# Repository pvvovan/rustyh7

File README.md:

# rustyh7
stm32h723zg simple app in Rust

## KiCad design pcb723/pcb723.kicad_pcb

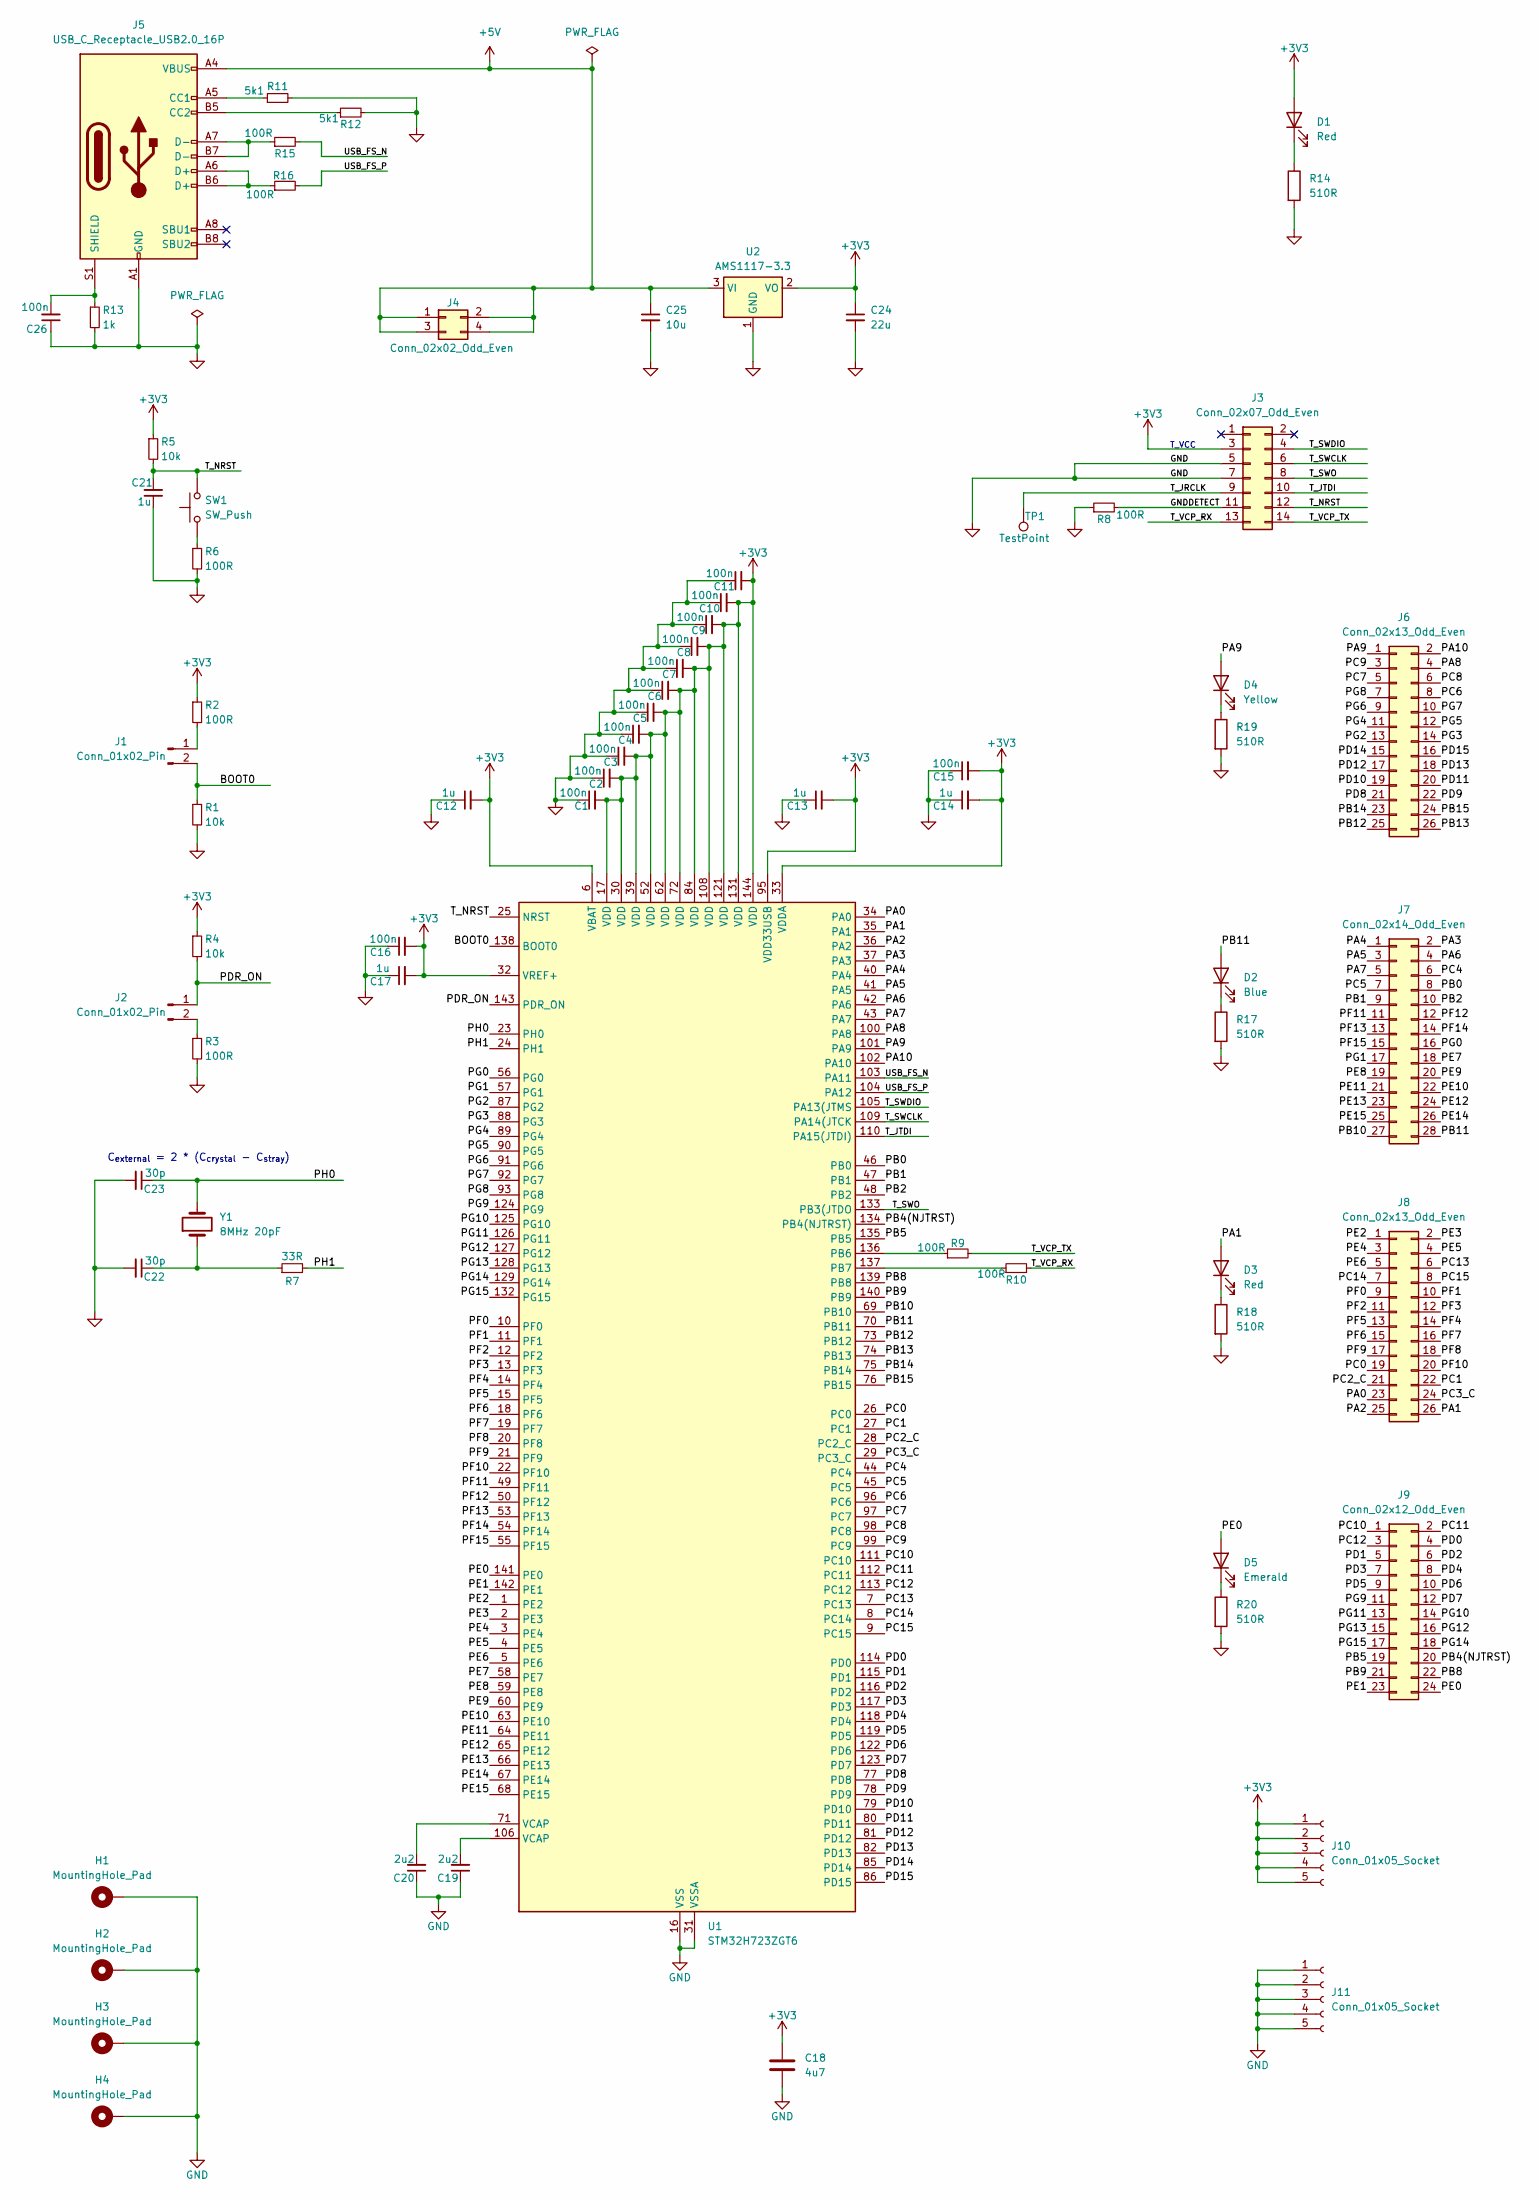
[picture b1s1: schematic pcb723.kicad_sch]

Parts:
C1, C2, C3, C4, C5, C6, C7, C8, C9, C10, C11, C15, C16, C26: 100n; C_0402_1005Metric; JLC# C307331
C12, C13, C14, C17, C21: 1u; C_0402_1005Metric; JLC# C52923
C18: 4u7; C_1206_3216Metric; JLC# C29823
C19, C20: 2u2; C_0805_2012Metric; JLC# C377773
C22, C23: 30p; C_0603_1608Metric; JLC# C1658
C24: 22u; C_0805_2012Metric; JLC# C45783
C25: 10u; C_1206_3216Metric; JLC# C13585
D1: Red; LED_0603_1608Metric; JLC# C2286
D2: Blue; LED_0805_2012Metric
D3: Red; LED_0805_2012Metric; JLC# C84256
D4: Yellow; LED_0805_2012Metric; JLC# C2296
D5: Emerald; LED_0805_2012Metric; JLC# C2297
H1, H2, H3, H4: MountingHole_Pad; MountingHole_3.2mm_M3_Pad_Via
J1, J2: Conn_01x02_Pin; PinHeader_1x02_P2.54mm_Vertical
J3: Conn_02x07_Odd_Even; PinHeader_2x07_P1.27mm_Vertical_SMD
J4: Conn_02x02_Odd_Even; PinSocket_2x02_P2.54mm_Vertical
J5: USB_C_Receptacle_USB2.0_16P; USB_C_Receptacle_GCT_USB4105-xx-A_16P_TopMnt_Horizontal
J6, J8: Conn_02x13_Odd_Even; PinSocket_2x13_P2.54mm_Vertical
J7: Conn_02x14_Odd_Even; PinSocket_2x14_P2.54mm_Vertical
J9: Conn_02x12_Odd_Even; PinSocket_2x12_P2.54mm_Vertical
J10, J11: Conn_01x05_Socket; PinSocket_1x05_P2.54mm_Vertical
R1, R4, R5: 10k; R_0402_1005Metric; JLC# C25744
R2, R3, R6, R8, R9, R10, R15, R16: 100R; R_0402_1005Metric; JLC# C25076
R7: 33R; R_0402_1005Metric; JLC# C25105
R11, R12: 5k1; R_0402_1005Metric; JLC# C25905
R13: 1k; R_0402_1005Metric; JLC# C11702
R14, R17, R18, R19, R20: 510R; R_0805_2012Metric_Pad1.20x1.40mm_HandSolder; JLC# C17734
SW1: SW_Push; SW_Push_1P1T_NO_6x6mm_H9.5mm
TP1: TestPoint; TestPoint_Plated_Hole_D2.0mm
U1: STM32H723ZGT6; LQFP-144_20x20mm_P0.5mm
U2: AMS1117-3.3; SOT-223-3_TabPin2; JLC# C6186
Y1: 8MHz 20pF; Crystal_SMD_5032-2Pin_5.0x3.2mm; JLC# C115962

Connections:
+3V3: C1.2, C2.2, C3.2, C4.2, C5.2, C6.2, C7.2, C8.2, C9.2, C10.2, C11.2, C12.2, C13.2, C14.2, C15.2, C16.2, C17.2, C18.1, C24.1, D1.2 (A), J3.3, J10.1, J10.2, J10.3, J10.4, J10.5, R2.1, R4.1, R5.1, U1.6 (VBAT), U1.17 (VDD), U1.30 (VDD), U1.32 (VREF+), U1.33 (VDDA), U1.39 (VDD), U1.52 (VDD), U1.62 (VDD), U1.72 (VDD), U1.84 (VDD), U1.95 (VDD33USB), U1.108 (VDD), U1.121 (VDD), U1.131 (VDD), U1.144 (VDD), U2.2 (VO)
+5V: C25.1, J4.1, J4.2, J4.3, J4.4, J5.A4 (VBUS), J5.A9 (VBUS), J5.B4 (VBUS), J5.B9 (VBUS), U2.3 (VI)
/BOOT0: J1.2, R1.1, U1.138 (BOOT0)
/GNDDETECT: J3.11, R8.2
/PA0: J8.23, U1.34 (PA0)
/PA1: D3.2 (A), J8.26, U1.35 (PA1)
/PA2: J8.25, U1.36 (PA2)
/PA3: J7.2, U1.37 (PA3)
/PA4: J7.1, U1.40 (PA4)
/PA5: J7.3, U1.41 (PA5)
/PA6: J7.4, U1.42 (PA6)
/PA7: J7.5, U1.43 (PA7)
/PA8: J6.4, U1.100 (PA8)
/PA9: D4.2 (A), J6.1, U1.101 (PA9)
/PA10: J6.2, U1.102 (PA10)
/PB0: J7.8, U1.46 (PB0)
/PB1: J7.9, U1.47 (PB1)
/PB2: J7.10, U1.48 (PB2)
/PB4(NJTRST): J9.20, U1.134 (PB4(NJTRST))
/PB5: J9.19, U1.135 (PB5)
/PB8: J9.22, U1.139 (PB8)
/PB9: J9.21, U1.140 (PB9)
/PB10: J7.27, U1.69 (PB10)
/PB11: D2.2 (A), J7.28, U1.70 (PB11)
/PB12: J6.25, U1.73 (PB12)
/PB13: J6.26, U1.74 (PB13)
/PB14: J6.23, U1.75 (PB14)
/PB15: J6.24, U1.76 (PB15)
/PC0: J8.19, U1.26 (PC0)
/PC1: J8.22, U1.27 (PC1)
/PC2_C: J8.21, U1.28 (PC2_C)
/PC3_C: J8.24, U1.29 (PC3_C)
/PC4: J7.6, U1.44 (PC4)
/PC5: J7.7, U1.45 (PC5)
/PC6: J6.8, U1.96 (PC6)
/PC7: J6.5, U1.97 (PC7)
/PC8: J6.6, U1.98 (PC8)
/PC9: J6.3, U1.99 (PC9)
/PC10: J9.1, U1.111 (PC10)
/PC11: J9.2, U1.112 (PC11)
/PC12: J9.3, U1.113 (PC12)
/PC13: J8.6, U1.7 (PC13)
/PC14: J8.7, U1.8 (PC14)
/PC15: J8.8, U1.9 (PC15)
/PD0: J9.4, U1.114 (PD0)
/PD1: J9.5, U1.115 (PD1)
/PD2: J9.6, U1.116 (PD2)
/PD3: J9.7, U1.117 (PD3)
/PD4: J9.8, U1.118 (PD4)
/PD5: J9.9, U1.119 (PD5)
/PD6: J9.10, U1.122 (PD6)
/PD7: J9.12, U1.123 (PD7)
/PD8: J6.21, U1.77 (PD8)
/PD9: J6.22, U1.78 (PD9)
/PD10: J6.19, U1.79 (PD10)
/PD11: J6.20, U1.80 (PD11)
/PD12: J6.17, U1.81 (PD12)
/PD13: J6.18, U1.82 (PD13)
/PD14: J6.15, U1.85 (PD14)
/PD15: J6.16, U1.86 (PD15)
/PDR_ON: J2.1, R4.2, U1.143 (PDR_ON)
/PE0: D5.2 (A), J9.24, U1.141 (PE0)
/PE1: J9.23, U1.142 (PE1)
/PE2: J8.1, U1.1 (PE2)
/PE3: J8.2, U1.2 (PE3)
/PE4: J8.3, U1.3 (PE4)
/PE5: J8.4, U1.4 (PE5)
/PE6: J8.5, U1.5 (PE6)
/PE7: J7.18, U1.58 (PE7)
/PE8: J7.19, U1.59 (PE8)
/PE9: J7.20, U1.60 (PE9)
/PE10: J7.22, U1.63 (PE10)
/PE11: J7.21, U1.64 (PE11)
/PE12: J7.24, U1.65 (PE12)
/PE13: J7.23, U1.66 (PE13)
/PE14: J7.26, U1.67 (PE14)
/PE15: J7.25, U1.68 (PE15)
/PF0: J8.9, U1.10 (PF0)
/PF1: J8.10, U1.11 (PF1)
/PF2: J8.11, U1.12 (PF2)
/PF3: J8.12, U1.13 (PF3)
/PF4: J8.14, U1.14 (PF4)
/PF5: J8.13, U1.15 (PF5)
/PF6: J8.15, U1.18 (PF6)
/PF7: J8.16, U1.19 (PF7)
/PF8: J8.18, U1.20 (PF8)
/PF9: J8.17, U1.21 (PF9)
/PF10: J8.20, U1.22 (PF10)
/PF11: J7.11, U1.49 (PF11)
/PF12: J7.12, U1.50 (PF12)
/PF13: J7.13, U1.53 (PF13)
/PF14: J7.14, U1.54 (PF14)
/PF15: J7.15, U1.55 (PF15)
/PG0: J7.16, U1.56 (PG0)
/PG1: J7.17, U1.57 (PG1)
/PG2: J6.13, U1.87 (PG2)
/PG3: J6.14, U1.88 (PG3)
/PG4: J6.11, U1.89 (PG4)
/PG5: J6.12, U1.90 (PG5)
/PG6: J6.9, U1.91 (PG6)
/PG7: J6.10, U1.92 (PG7)
/PG8: J6.7, U1.93 (PG8)
/PG9: J9.11, U1.124 (PG9)
/PG10: J9.14, U1.125 (PG10)
/PG11: J9.13, U1.126 (PG11)
/PG12: J9.16, U1.127 (PG12)
/PG13: J9.15, U1.128 (PG13)
/PG14: J9.18, U1.129 (PG14)
/PG15: J9.17, U1.132 (PG15)
/PH0: C23.1, U1.23 (PH0), Y1.2
/PH1: R7.2, U1.24 (PH1)
/T_JRCLK: J3.9, TP1.1
/T_JTDI: J3.10, U1.110 (PA15(JTDI))
/T_NRST: C21.2, J3.12, R5.2, SW1.2, U1.25 (NRST)
/T_SWCLK: J3.6, U1.109 (PA14(JTCK)
/T_SWDIO: J3.4, U1.105 (PA13(JTMS)
/T_SWO: J3.8, U1.133 (PB3(JTDO)
/T_VCP_RX: J3.13, R10.2
/T_VCP_TX: J3.14, R9.2
/USB_FS_N: R15.2, U1.103 (PA11)
/USB_FS_P: R16.2, U1.104 (PA12)
GND: C1.1, C2.1, C3.1, C4.1, C5.1, C6.1, C7.1, C8.1, C9.1, C10.1, C11.1, C12.1, C13.1, C14.1, C15.1, C16.1, C17.1, C18.2, C19.1, C20.1, C21.1, C22.2, C23.2, C24.2, C25.2, C26.1, H1.1, H2.1, H3.1, H4.1, J3.5, J3.7, J5.A1 (GND), J5.A12 (GND), J5.B1 (GND), J5.B12 (GND), J11.1, J11.2, J11.3, J11.4, J11.5, R1.2, R3.2, R6.2, R8.1, R11.2, R12.2, R13.2, R14.2, R17.2, R18.2, R19.2, R20.2, U1.16 (VSS), U1.31 (VSSA), U1.38 (VSS), U1.51 (VSS), U1.61 (VSS), U1.83 (VSS), U1.94 (VSS), U1.107 (VSS), U1.120 (VSS), U1.130 (VSS), U2.1 (GND)
unnamed: C19.2, U1.106 (VCAP)
unnamed: C20.2, U1.71 (VCAP)
unnamed: C22.1, R7.1, Y1.1
unnamed: D1.1 (K), R14.1
unnamed: D2.1 (K), R17.1
unnamed: D3.1 (K), R18.1
unnamed: D4.1 (K), R19.1
unnamed: D5.1 (K), R20.1
unnamed: J1.1, R2.2
unnamed: J2.2, R3.1
unnamed: J5.A5 (CC1), R11.1
unnamed: J5.B5 (CC2), R12.1
unnamed: J5.A6 (D+), J5.B6 (D+), R16.1
unnamed: J5.A7 (D-), J5.B7 (D-), R15.1
unnamed: C26.2, J5.S1 (SHIELD), R13.1
unnamed: R6.1, SW1.1
unnamed: R9.1, U1.136 (PB6)
unnamed: R10.1, U1.137 (PB7)

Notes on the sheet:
C_{external} = 2 * (C_{crystal} - C_{stray})
T_VCC

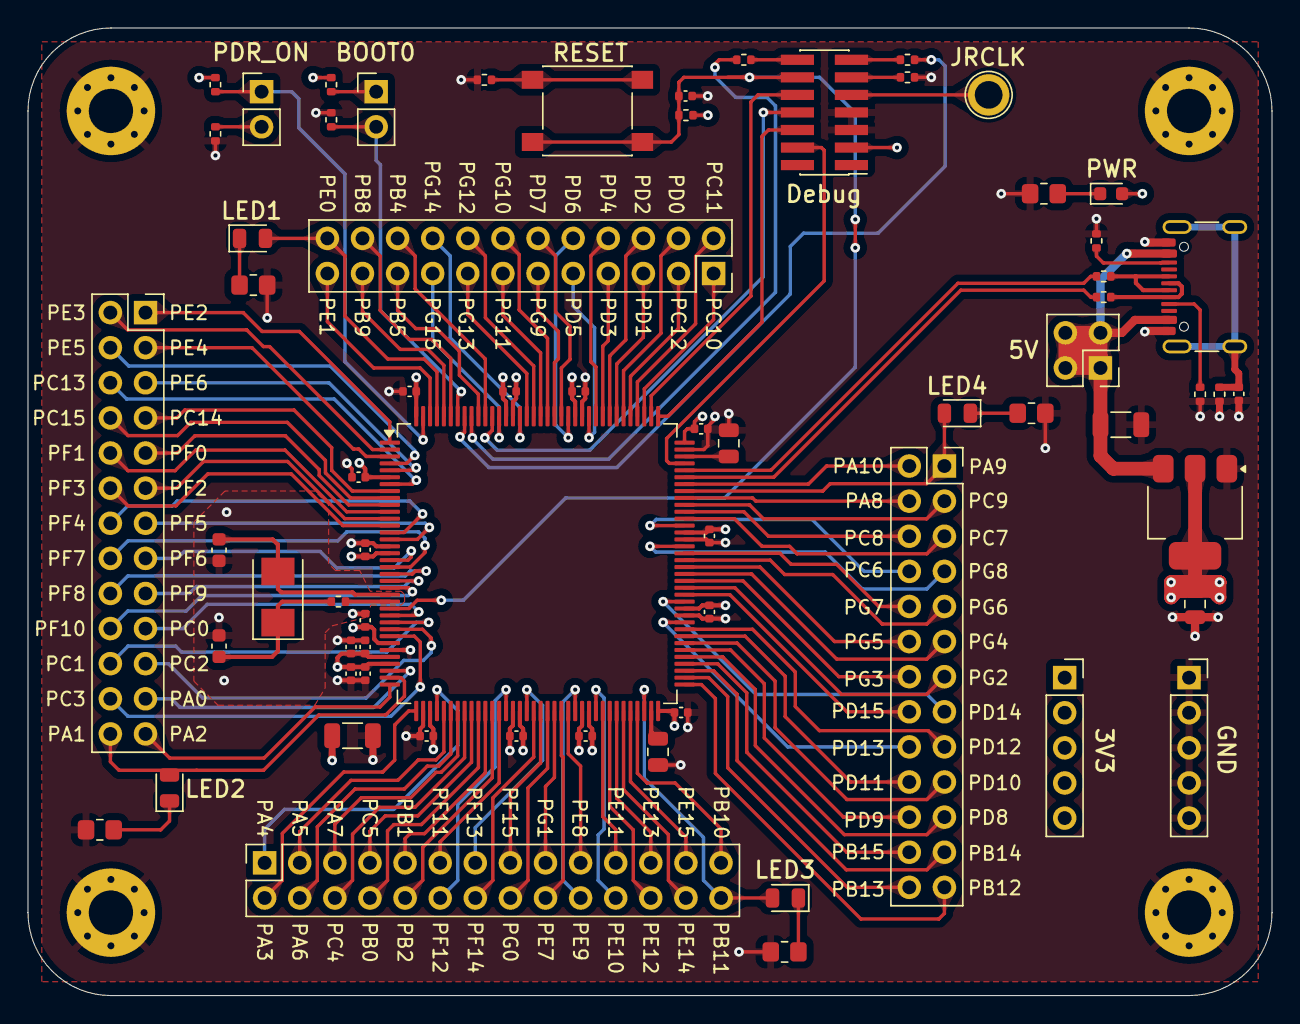
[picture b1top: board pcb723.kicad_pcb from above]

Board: 4 copper layers, 90.0 x 70.0 mm, 71 parts (0 on the bottom side), 140 nets.

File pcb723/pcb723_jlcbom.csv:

Comment,Designator,Footprint,JLCPCB Part#
100n,"C1, C2, C3, C4, C5, C6, C7, C8, C9, C10, C11, C15, C16, C26",Capacitor_SMD:C_0402_1005Metric,C307331
1u,"C12, C13, C14, C17, C21",Capacitor_SMD:C_0402_1005Metric,C52923
4u7,"C18",Capacitor_SMD:C_1206_3216Metric,C29823
2u2,"C19, C20",Capacitor_SMD:C_0805_2012Metric,C377773
30p,"C22, C23",Capacitor_SMD:C_0603_1608Metric,C1658
22u,"C24",Capacitor_SMD:C_0805_2012Metric,C45783
10u,"C25",Capacitor_SMD:C_1206_3216Metric,C13585
Red,"D1",LED_SMD:LED_0603_1608Metric,C2286
Red,"D3",LED_SMD:LED_0805_2012Metric,C84256
Yellow,"D4",LED_SMD:LED_0805_2012Metric,C2296
Emerald,"D5",LED_SMD:LED_0805_2012Metric,C2297
10k,"R1, R4, R5",Resistor_SMD:R_0402_1005Metric,C25744
5k1,"R11, R12",Resistor_SMD:R_0402_1005Metric,C25905
1k,"R13",Resistor_SMD:R_0402_1005Metric,C11702
510R,"R14, R17, R18, R19, R20",Resistor_SMD:R_0805_2012Metric_Pad1.20x1.40mm_HandSolder,C17734
100R,"R2, R3, R6, R8, R9, R10, R15, R16",Resistor_SMD:R_0402_1005Metric,C25076
33R,"R7",Resistor_SMD:R_0402_1005Metric,C25105
AMS1117-3.3,"U2",Package_TO_SOT_SMD:SOT-223-3_TabPin2,C6186
8MHz 20pF,"Y1",Crystal:Crystal_SMD_5032-2Pin_5.0x3.2mm,C115962

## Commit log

2023-05-07 Initial app
2023-05-07 Initial build
2023-05-07 Debug with ST-Link
2023-05-07 Init RAM
2023-05-07 Add vector table
2023-05-07 Enable FPU
2023-05-12 Set stack pointer
2023-06-11 clear files
2023-06-11 Add simple
2023-06-11 Add cargo config
2023-06-11 Debug simple
2023-07-29 add mybreakpoint
2023-07-29 Add SysTick
2023-07-29 10Hz SysTick IRQ
2023-07-30 Remove pub in ISRs
2023-07-30 Add atomic context
2023-08-05 Gpio driver
2023-08-05 LED blink
2023-08-05 set flash latency
2023-08-05 init power control
2023-08-06 Enable ICache
2023-08-06 Enable DCache
2023-08-06 Reverse for-loop
2023-08-06 Remove system_init()
2023-08-06 read/write volatile
2023-08-06 Enable HSE crystal oscillator
2023-08-06 Set HSE as PLL source
2023-08-06 Enable PLL1P and PLL1R
2023-08-06 Run CPU at 550 MHz
2023-08-07 Blink 1Hz
2023-08-07 Add barriers in isr.rs
2023-08-07 Add Cortex-M7 user guide
2023-08-07 Refactor into GPIO_BASE
2023-08-07 Atomic sync in gpio take()
2023-08-07 Keep unused pins mode
2023-08-07 Remove array size
2023-09-02 Extract flash driver
2023-09-02 Unlock flash
2023-09-02 flash read/write
2023-09-02 Flash sector 5
2023-09-02 flash read/write at blink
2023-09-02 128K flash sector size
2023-09-03 Draft flash store/erase
2023-09-03 Program flash with cache
2024-03-02 Initial KiCAD project
2024-03-02 Add 100nF capacitors
2024-03-02 Place 100nF capacitors
2024-03-02 Add reference capacitors
2024-03-02 Add jumpers
2024-03-03 Add ceramic crystal
2024-03-03 Add USB-C connector
2024-03-03 Add shielding
2024-03-03 Add PWR LED
2024-03-03 Place decoupling capacitors
2024-03-03 Connect external crystal clock
2024-03-03 Add 26 pin breakout
2024-03-03 Connect starting breakout pins
2024-03-03 Connect 28-pin socket header
2024-03-03 Add left breakout connector
2024-03-03 Add 24 pin socket
2024-03-04 Add 4 LEDs
2024-03-04 Complete schematic
2024-03-04 Copper pour in front and back layers
2024-03-04 Add power socket headers
2024-03-04 JTAG connector 3D model
2024-03-04 Push button 3D model
2024-03-04 Route USB-C connector
2024-03-04 Route LED4
2024-03-04 Move JTAG connector higher
2024-03-04 Route LED1
2024-03-04 Route LED3
2024-03-04 LED3 labels
2024-03-05 Route LED2 top
2024-03-05 Route LED2
2024-03-05 Label LED2
2024-03-05 Thermal relief zones
2024-03-05 Replace 8MHz
2024-03-05 Crystal 3D model
2024-03-05 BOM positioning python script
2024-03-05 Generate gerber/drill files
2024-03-05 Generate positioning file
2024-03-05 Zip gerber files
2024-03-05 Generate BOM
2024-03-05 Create JLC POS file
2024-03-05 Adapt JLC BOM POS python script
2024-03-05 Generate JLC POS/BOM files
2024-03-05 Fix BOM/POS script
2024-03-05 Update resistor footprints
2024-03-05 Update footprints in PCB
2024-03-05 Remove generated fabrication output
2024-03-05 Add tear drops
2024-03-05 Generate gerber files
2024-03-05 Generate POS/BOM files
2024-03-05 Regenerate gerbers
2024-03-05 Updated BOM/POS files
2024-03-05 Add MCU into BOM
2024-03-05 Rotate MCU
2024-03-05 PCB 3D view screenshot
2024-03-10 R14 footprint warning fix
2024-03-10 User LED R footprint warning fixes
2024-03-10 Capacitor footprint warning fix
2024-03-10 Generate BOM/POS files
2024-03-10 Finalize order files
2024-03-16 Update footprints of capacitors
2024-03-16 Update footprints of resistors
    Generate fabrication output
2024-03-16 Generate jlcpcb BOM/POS files
    Rotate U2
2024-03-28 Schematic in pdf
